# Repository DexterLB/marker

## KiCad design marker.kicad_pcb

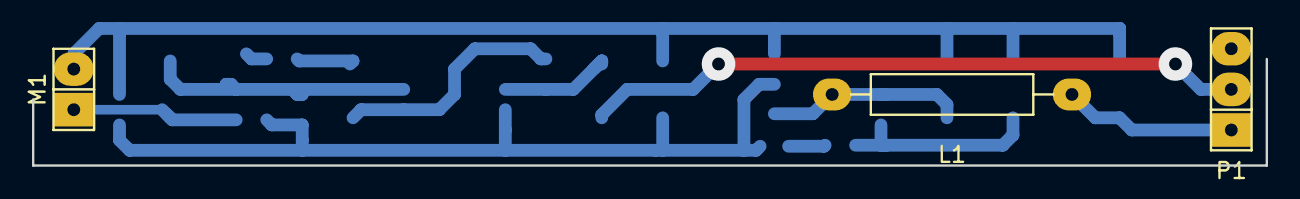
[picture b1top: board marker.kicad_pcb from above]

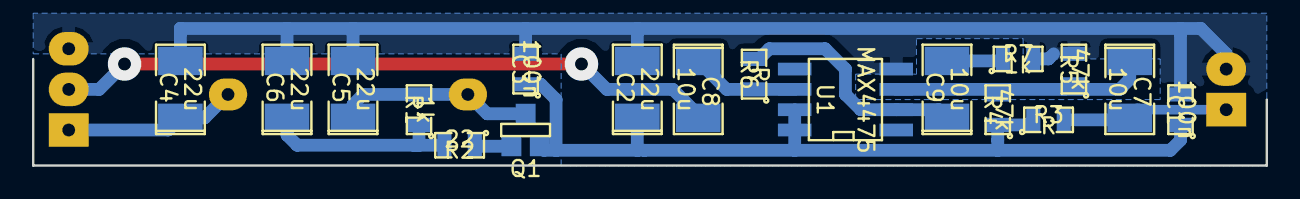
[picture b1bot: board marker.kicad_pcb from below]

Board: 2 copper layers, 77.2 x 6.7 mm, 21 parts (18 on the bottom side), 12 nets.

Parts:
C1, C3: 100n; SMD-0805
C2, C4, C5, C6: 22u; SMD-1210_Pol
C7, C8, C9: 10u; SMD-1210_Pol
L1: INDUCTOR_SMALL; Resistor_Horizontal_RM15mm
M1: MIC; Pin_Header_Straight_1x02
P1: Cable; Pin_Header_Straight_1x03
Q1: NPN; SOT-23-EBC
R1, R7: 1k; SMD-0805
R2: 22; SMD-0805
R3, R6: R; SMD-0805
R4, R5: 47k; SMD-0805
U1: MAX4475; SOIC-8-N

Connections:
GND: C1.2, C2.2, C3.2, C4.2, C5.2, C6.2, M1.2, P1.3, R5.2, R7.2, U1.4
unnamed: C1.1, C2.1, C3.1, Q1.1, R3.1, R4.1, U1.7, U1.8
unnamed: C4.1, L1.1, P1.1
unnamed: C5.1, L1.2, Q1.3, R1.2
unnamed: C6.1, R1.1, R2.2
unnamed: C7.1, R4.2, R5.1, U1.3
unnamed: C7.2, M1.1, R3.2
unnamed: C8.1, R6.1, U1.6
unnamed: C8.2, P1.2
unnamed: C9.1, R6.2, U1.2
unnamed: C9.2, R7.1
unnamed: Q1.2, R2.1

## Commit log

2015-09-18 initial commit, add opamp
2015-09-18 schematic draft
2015-09-18 plot schematic
2015-09-18 convert svg to pdf
2015-09-18 annotate
2015-09-19 add transistor-based filter
2015-11-09 some work on the pcb
2015-11-12 finish working on pcb
2015-11-12 add netlist
2015-11-12 add print
